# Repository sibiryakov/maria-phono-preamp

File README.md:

# Moving magnet phono preamp Maria

* Точность соответствия RIAA - 0.3 dB в среднем, 0.11 в интервале 125-8000 Гц,
* Поддерживаются только Moving Magnet (MM) картриджи,
* Усиление +30 dB, на частоте 1 kHz,
* Номинальное входное напряжение - 5 mV
* Входное сопротивление - 47 кОм
* Входная ёмкость - 100-470 пФ, впаивается пользователем
* Напряжение питания - +15В, -15В
* Потребляемый ток - ~100mA
* Максимальный уровень выходного сигнала 13В (25 dBu)
* THD на частоте 1 kHz - 0.004 %
* Шум, 1 kHz на уровне -120 dBu, 50hz   -100dbu
* Взаимное проникновение каналов 1 kHz (0 dBu)   -66 dBu

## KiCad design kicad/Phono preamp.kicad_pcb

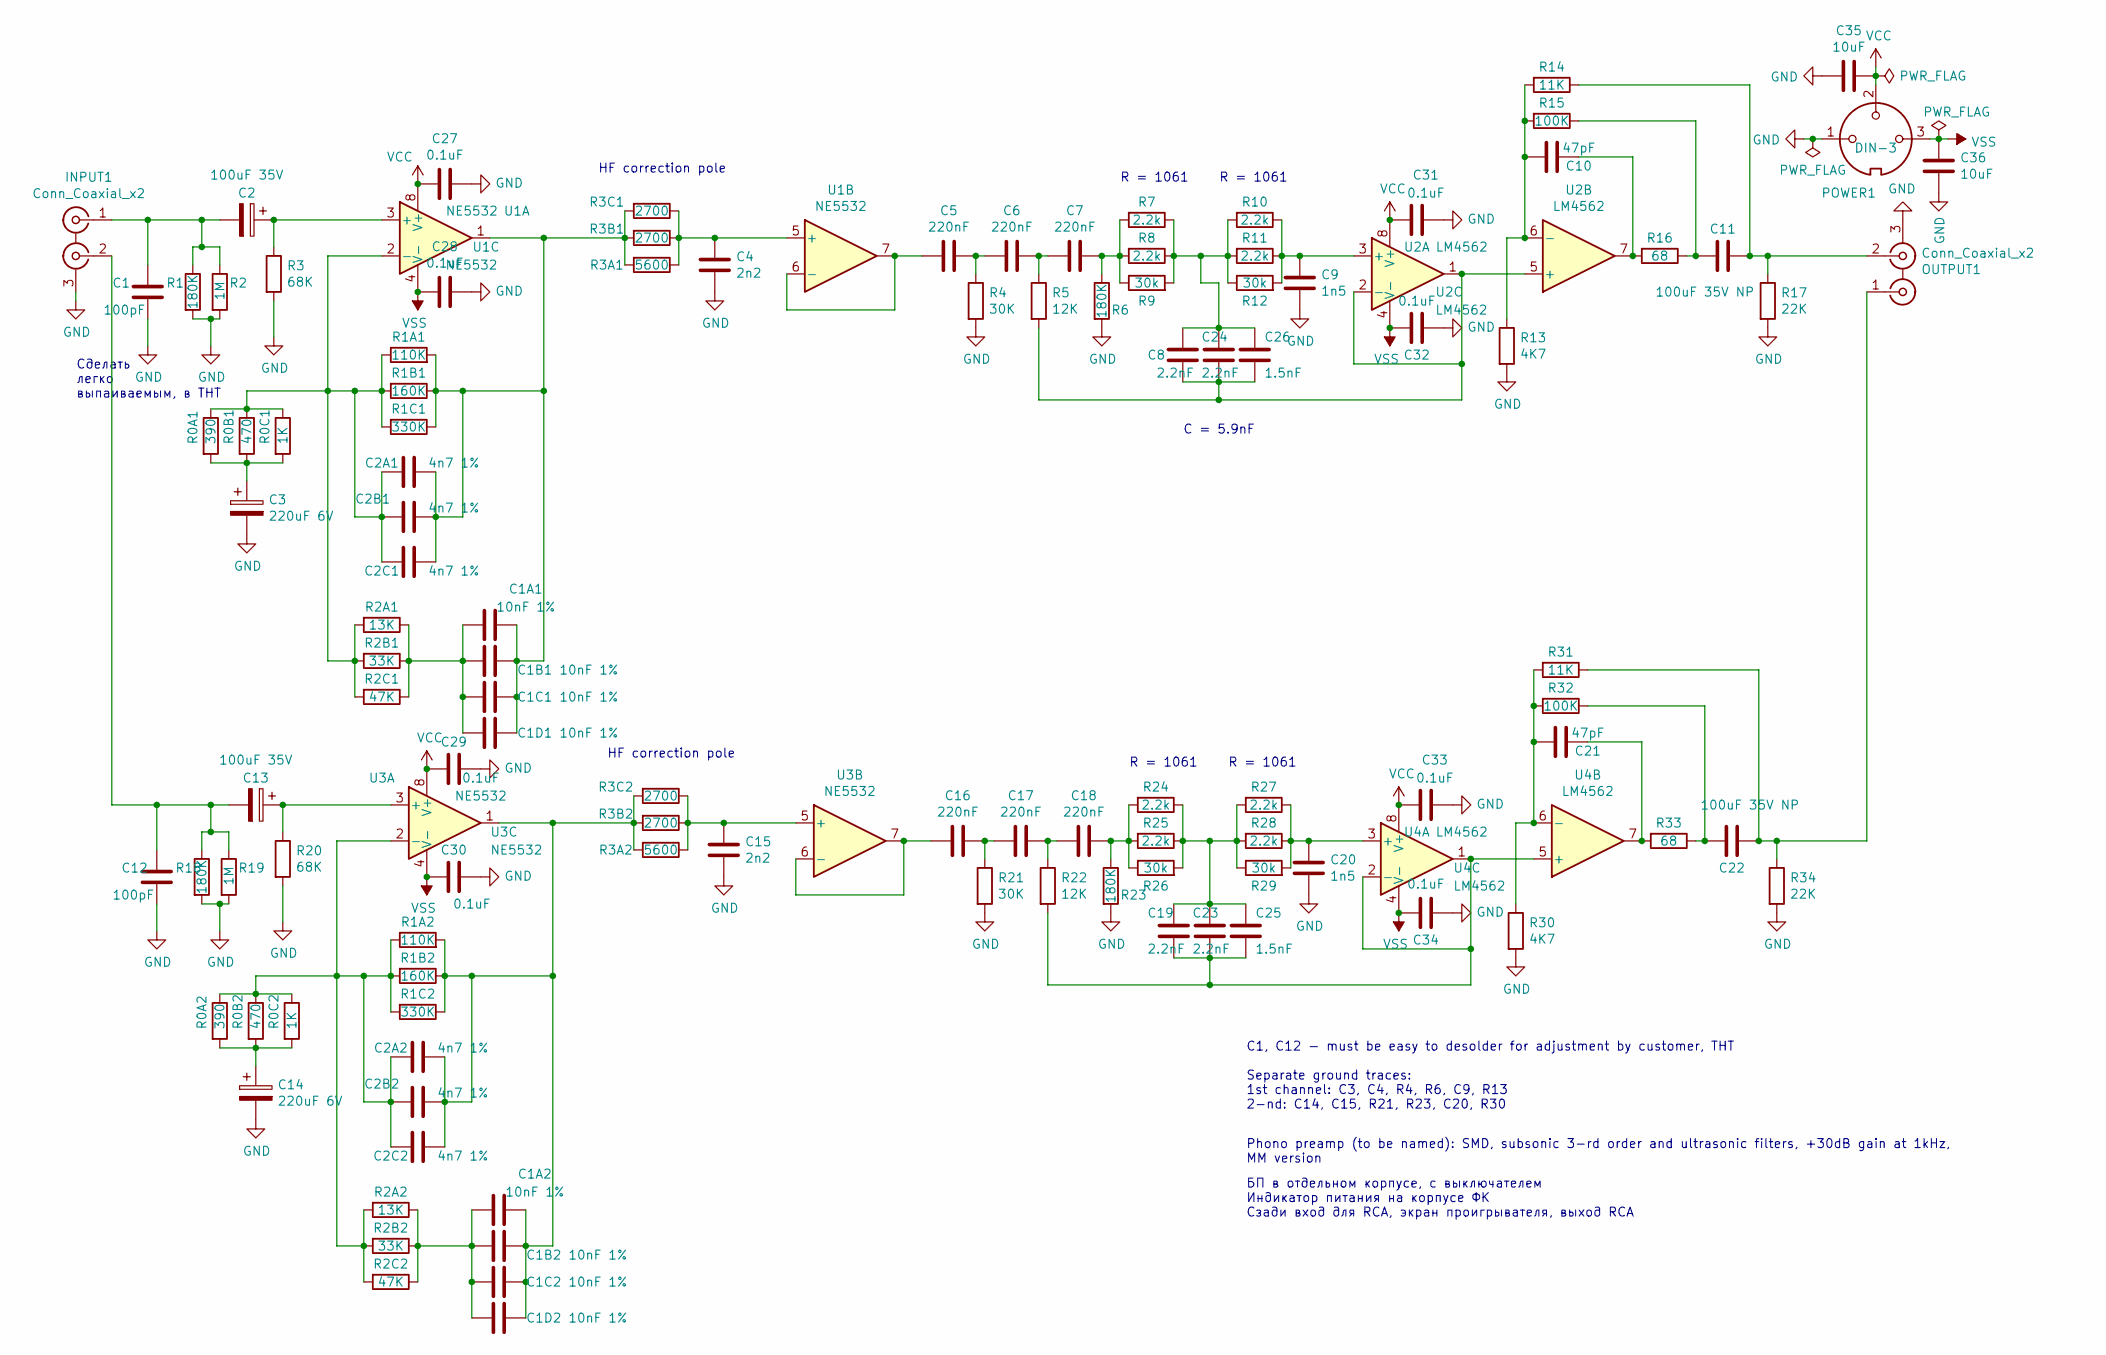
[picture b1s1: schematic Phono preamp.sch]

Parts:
C1, C12: 100pF; C_Rect_L7.0mm_W4.5mm_P5.00mm
C1A1, C1A2, C1B1, C1B2, C1C1, C1C2, C1D1, C1D2: 10nF 1%; C_0805_2012Metric
C2, C13: 100uF 35V; CP_Radial_D8.0mm_P5.00mm
C2A1, C2A2, C2B1, C2B2, C2C1, C2C2: 4n7 1%; C_0805_2012Metric
C3, C14: 220uF 6V; CP_Radial_D6.3mm_P2.50mm
C4, C15: 2n2; C_0805_2012Metric
C5, C6, C7, C16, C17, C18: 220nF; C_Axial_L12.0mm_D8.5mm_P20.00mm_Horizontal
C8, C19, C23, C24: 2.2nF; C_0805_2012Metric
C9, C20: 1n5; C_0805_2012Metric
C10, C21: 47pF; C_1206_3216Metric
C11, C22: 100uF 35V NP; C_Radial_D16.0mm_H25.0mm_P7.50mm
C25, C26: 1.5nF; C_0805_2012Metric
C27, C28, C29, C30, C31, C32, C33, C34: 0.1uF; C_1206_3216Metric
C35, C36: 10uF; C_1206_3216Metric
INPUT1: Conn_Coaxial_x2; RCA_8.3mm_CLIFF_FC68405_Horizontal
OUTPUT1: Conn_Coaxial_x2; RCA_8.3mm_CLIFF_FC68405_Horizontal
POWER1: DIN-3; PinHeader_1x03_P2.54mm_Vertical
R0A1, R0A2: 390; R_1206_3216Metric
R0B1, R0B2: 470; R_1206_3216Metric
R0C1, R0C2: 1K; R_1206_3216Metric
R1, R6, R18, R23: 180K; R_1206_3216Metric
R1A1, R1A2: 110K; R_1206_3216Metric
R1B1, R1B2: 160K; R_1206_3216Metric
R1C1, R1C2: 330K; R_1206_3216Metric
R2, R19: 1M; R_1206_3216Metric
R2A1, R2A2: 13K; R_1206_3216Metric
R2B1, R2B2: 33K; R_1206_3216Metric
R2C1, R2C2: 47K; R_1206_3216Metric
R3, R20: 68K; R_1206_3216Metric
R3A1, R3A2: 5600; R_1206_3216Metric
R3B1, R3B2, R3C1, R3C2: 2700; R_1206_3216Metric
R4, R21: 30K; R_1206_3216Metric
R5, R22: 12K; R_1206_3216Metric
R7, R8, R10, R11, R24, R25, R27, R28: 2.2k; R_1206_3216Metric
R9, R12, R26, R29: 30k; R_1206_3216Metric
R13, R30: 4K7; R_1206_3216Metric
R14, R31: 11K; R_1206_3216Metric
R15, R32: 100K; R_1206_3216Metric
R16, R33: 68; R_1206_3216Metric
R17, R34: 22K; R_1206_3216Metric
U1, U3: NE5532; SOIC-8_3.9x4.9mm_P1.27mm
U2, U4: LM4562; SOIC-8_3.9x4.9mm_P1.27mm

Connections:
GND: C1.2, C3.2, C4.2, C9.2, C12.2, C14.2, C15.2, C20.2, C27.1, C28.1, C29.1, C30.1, C31.1, C32.1, C33.1, C34.1, C35.1, C36.1, INPUT1.3 (EXT), OUTPUT1.3 (EXT), POWER1.1, R1.2, R2.2, R3.2, R4.2, R6.2, R13.2, R17.2, R18.2, R19.2, R20.2, R21.2, R23.2, R30.2, R34.2
unnamed: C1.1, C2.2, INPUT1.1 (IN1), R1.1, R2.1
unnamed: C1A1.1, C1B1.1, C1C1.1, C1D1.1, C2A1.2, C2B1.1, C2C1.1, R1A1.2, R1B1.1, R1C1.1, R3A1.2, R3B1.2, R3C1.2, U1.1
unnamed: C1A1.2, C1B1.2, C1C1.2, C1D1.2, R2A1.1, R2B1.1, R2C1.1
unnamed: C1A2.1, C1B2.1, C1C2.1, C1D2.1, C2A2.2, C2B2.1, C2C2.1, R1A2.2, R1B2.1, R1C2.1, R3A2.2, R3B2.2, R3C2.2, U3.1
unnamed: C1A2.2, C1B2.2, C1C2.2, C1D2.2, R2A2.1, R2B2.1, R2C2.1
unnamed: C2.1, R3.1, U1.3 (+)
unnamed: C2A1.1, C2B1.2, C2C1.2, R0A1.1, R0B1.1, R0C1.1, R1A1.1, R1B1.2, R1C1.2, R2A1.2, R2B1.2, R2C1.2, U1.2 (-)
unnamed: C2A2.1, C2B2.2, C2C2.2, R0A2.1, R0B2.1, R0C2.1, R1A2.1, R1B2.2, R1C2.2, R2A2.2, R2B2.2, R2C2.2, U3.2 (-)
unnamed: C3.1, R0A1.2, R0B1.2, R0C1.2
unnamed: C4.1, R3A1.1, R3B1.1, R3C1.1, U1.5 (+)
unnamed: C5.1, C6.2, R4.1
unnamed: C5.2, U1.6 (-), U1.7
unnamed: C6.1, C7.2, R5.1
unnamed: C7.1, R6.1, R7.2, R8.2, R9.1
unnamed: C9.1, R10.1, R11.1, R12.2, U2.3 (+)
unnamed: C10.1, R16.2, U2.7
unnamed: C10.2, R13.1, R14.2, R15.2, U2.6 (-)
unnamed: C11.1, OUTPUT1.2 (IN2), R14.1, R17.1
unnamed: C11.2, R15.1, R16.1
unnamed: C12.1, C13.2, INPUT1.2 (IN2), R18.1, R19.1
unnamed: C13.1, R20.1, U3.3 (+)
unnamed: C14.1, R0A2.2, R0B2.2, R0C2.2
unnamed: C15.1, R3A2.1, R3B2.1, R3C2.1, U3.5 (+)
unnamed: C16.1, C17.2, R21.1
unnamed: C16.2, U3.6 (-), U3.7
unnamed: C17.1, C18.2, R22.1
unnamed: C18.1, R23.1, R24.2, R25.2, R26.1
unnamed: C19.1, C23.1, C25.1, R24.1, R25.1, R26.2, R27.2, R28.2, R29.1
unnamed: C19.2, C23.2, C25.2, R22.2, U4.1, U4.2 (-), U4.5 (+)
unnamed: C20.1, R27.1, R28.1, R29.2, U4.3 (+)
unnamed: C21.1, R33.2, U4.7
unnamed: C21.2, R30.1, R31.2, R32.2, U4.6 (-)
unnamed: C22.1, R32.1, R33.1
unnamed: C22.2, OUTPUT1.1 (IN1), R31.1, R34.1
unnamed: C8.1, C24.1, C26.1, R7.1, R8.1, R9.2, R10.2, R11.2, R12.1
unnamed: C8.2, C24.2, C26.2, R5.2, U2.1, U2.2 (-), U2.5 (+)
VCC: C27.2, C29.2, C31.2, C33.2, C35.2, POWER1.2, U1.8 (V+), U2.8 (V+), U3.8 (V+), U4.8 (V+)
VSS: C28.2, C30.2, C32.2, C34.2, C36.2, POWER1.3, U1.4 (V-), U2.4 (V-), U3.4 (V-), U4.4 (V-)

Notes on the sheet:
Phono preamp (to be named): SMD, subsonic 3-rd order and ultrasonic filters, +30dB gain at 1kHz, MM version
HF correction pole
Сделать легко выпаиваемым, в THT
БП в отдельном корпусе, с выключателем Индикатор питания на корпусе ФК Сзади вход для RCA, экран проигрывателя, выход RCA
R = 1061
C = 5.9nF
C1, C12 - must be easy to desolder for adjustment by customer, THT Separate ground traces: 1st channel: C3, C4, R4, R6, C9, R13 2-nd: C14, C15, R21, R23, C20, R30

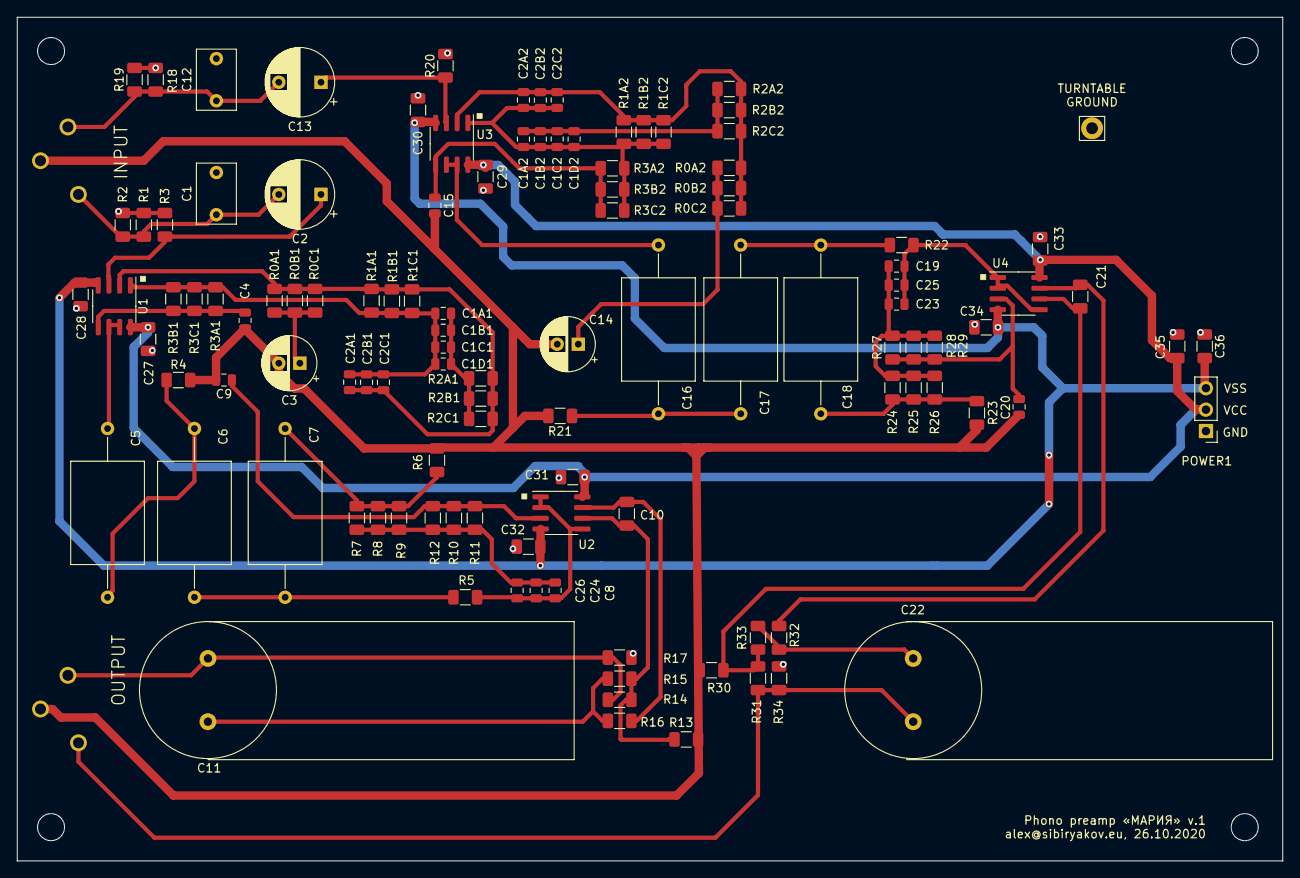
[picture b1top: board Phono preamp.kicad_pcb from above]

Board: 2 copper layers, 150.0 x 100.0 mm, 115 parts (0 on the bottom side), 39 nets.

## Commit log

2021-01-13 specs
2021-01-13 drawings, schematic, pcb
2021-01-13 RCA connector Footprint
